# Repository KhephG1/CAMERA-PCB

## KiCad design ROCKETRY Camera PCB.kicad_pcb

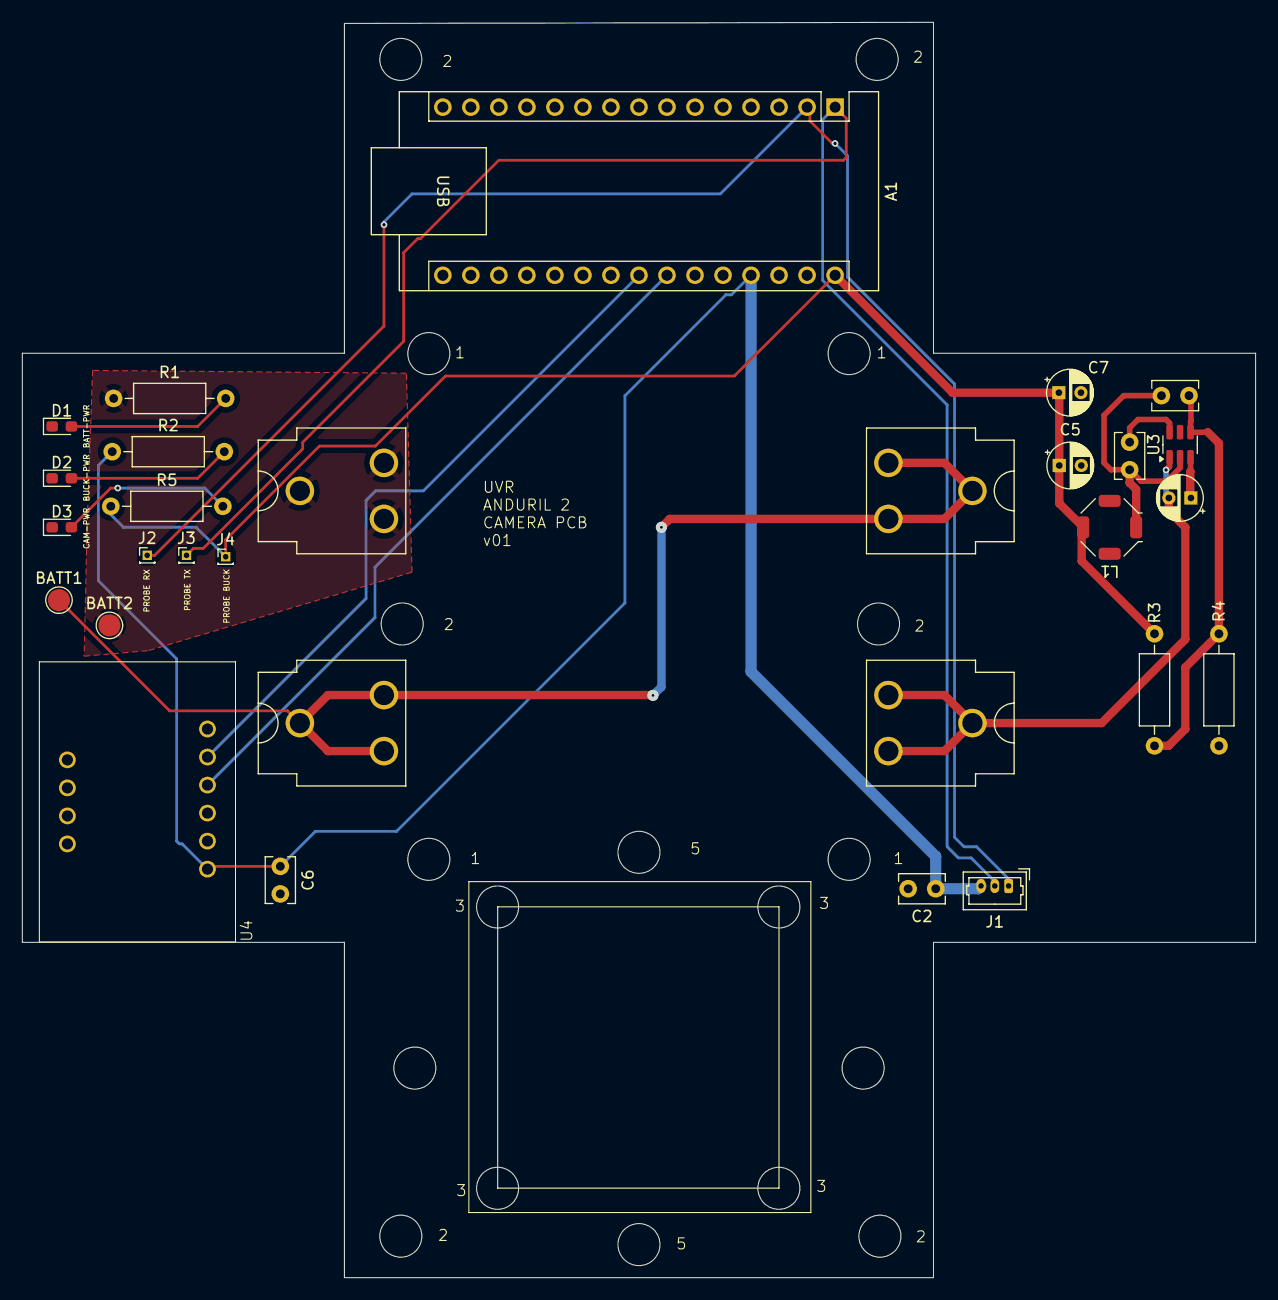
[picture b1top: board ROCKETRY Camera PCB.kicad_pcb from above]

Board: 2 copper layers, 111.8 x 113.8 mm, 27 parts (0 on the bottom side), 16 nets.

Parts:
A1: Arduino_Nano_v2.x; Arduino_Nano
BATT1, BATT2: TestPoint; TestPoint_Pad_D2.0mm
C1: 10uF; CP_Radial_D4.0mm_P2.00mm
C2, C6: 100nF; C_Rect_L4.0mm_W2.5mm_P2.50mm
C3: 200nF; C_Rect_L4.0mm_W2.5mm_P2.50mm
C4: 20pF; C_Rect_L4.0mm_W2.5mm_P2.50mm
C5, C7: 22uF; CP_Radial_D4.0mm_P2.00mm
D1, D2, D3: LED; LED_0603_1608Metric_Pad1.05x0.95mm_HandSolder
J1: Conn_01x03_Pin; Molex_PicoBlade_53047-0310_1x03_P1.25mm_Vertical
J2, J3, J4: Conn_01x01_Pin; PinHeader_1x01_P1.00mm_Vertical
L1: 4.7uH; L_Bourns_SRU5016_5.2x5.2mm
R1, R2, R4, R5: 10k; R_Axial_DIN0207_L6.3mm_D2.5mm_P10.16mm_Horizontal
R3: 52k; R_Axial_DIN0207_L6.3mm_D2.5mm_P10.16mm_Horizontal
U1, U2: 3.4v; BatteryClip_Keystone_54_D16-19mm
U3: AP62200WU; TSOT-23-6
U4: ADX375L

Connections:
/5V: A1.30 (VIN), C5.1, C7.1, J4.1, L1.2, R3.1, R5.1
/+5V: A1.27 (+5V), C2.1, C6.1, J1.3, R2.1, U4.5 (VIN)
/A4: A1.23 (A4), U4.8 (SDA)
/A5: A1.24 (A5), U4.7 (SCL)
/V-BATT+: BATT2.1, C1.1, R1.1, U1.1 (+), U3.3 (VIN)
GND: A1.4 (GND), A1.29 (GND), C2.2, C5.2, C6.2, C7.2, R4.2, U4.1 (GND), U4.6 (GND)
unnamed: A1.2 (D0/RX), J1.1, J2.1
unnamed: A1.1 (D1/TX), J1.2, J3.1
unnamed: D1.2 (A), R1.2
unnamed: D2.2 (A), R2.2
unnamed: D3.2 (A), R5.2
unnamed: BATT1.1, U1.2 (-), U2.1 (+)
unnamed: C1.2, U2.2 (-), U3.1 (GND)
unnamed: C3.2, U3.6 (BST)
unnamed: C4.2, R3.2, R4.1, U3.4 (FB)
unnamed: C3.1, C4.1, L1.1, U3.2 (SW)
